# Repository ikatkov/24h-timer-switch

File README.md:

# 24h timer switch

# Fabrication

See kicad files.

## BOM
| Id | Designator | Package | Designation | Value | 
| ------------- | ------------- | ------------- | ------------- |------------- |

## PCB

<a href="https://oshpark.com/shared_projects/55EIuuMn"></img></a>

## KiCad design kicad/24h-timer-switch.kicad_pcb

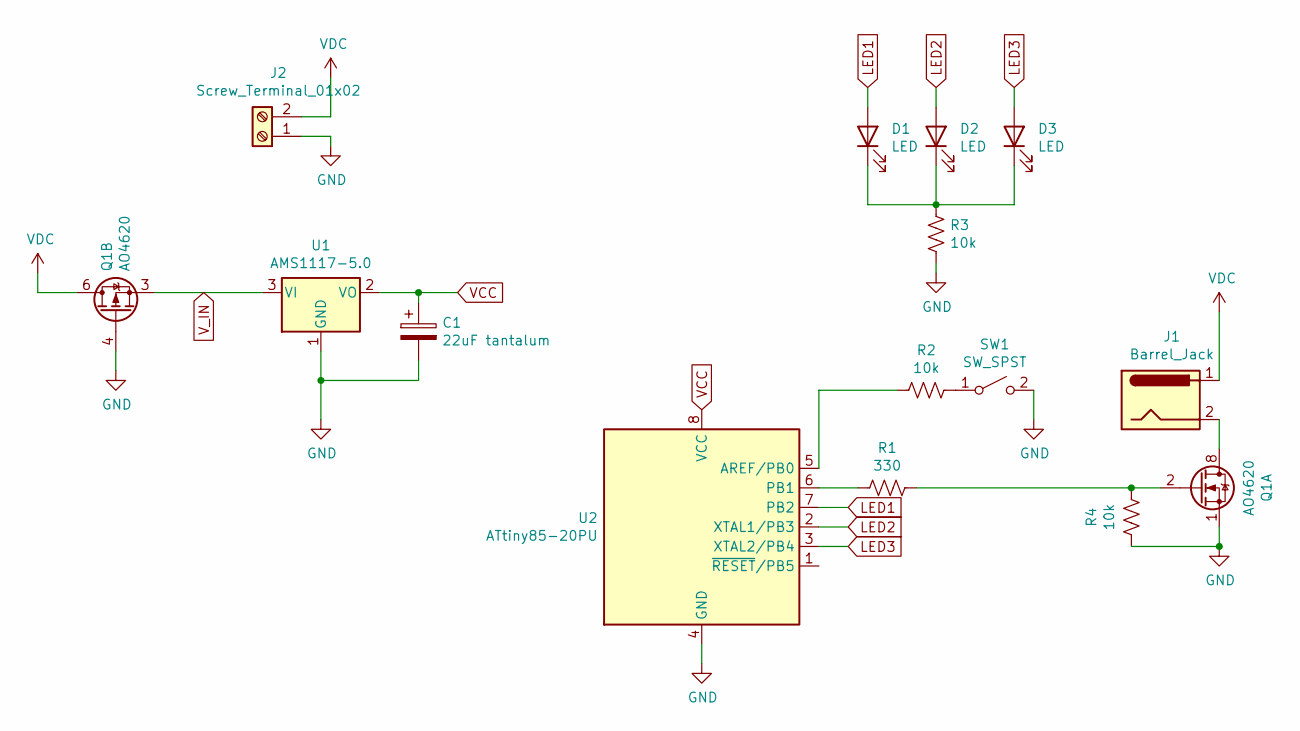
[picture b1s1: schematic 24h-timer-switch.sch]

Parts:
C1: 22uF tantalum; CP_Radial_D5.0mm_P2.50mm
D1, D2, D3: LED; LED_D5.0mm
J1: Barrel_Jack; BarrelJack_Horizontal
J2: Screw_Terminal_01x02; TerminalBlock_MetzConnect_Type011_RT05502HBWC_1x02_P5.00mm_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
Q1: AO4620; SOIC-8_3.9x4.9mm_P1.27mm
R1: 330; R_Axial_DIN0207_L6.3mm_D2.5mm_P2.54mm_Vertical
R2, R3, R4: 10k; R_Axial_DIN0207_L6.3mm_D2.5mm_P2.54mm_Vertical
SW1: SW_SPST; SW_PUSH_6mm_H9.5mm
U1: AMS1117-5.0; SOT-223-3_TabPin2
U2: ATtiny85-20PU; DIP-8_W7.62mm

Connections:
GND: C1.2, J2.1, Q1.1 (S), Q1.4 (G), R3.2, R4.2, SW1.2 (B), U1.1 (GND), U2.4 (GND)
LED1: D1.2 (A), U2.7 (PB2)
LED2: D2.2 (A), U2.2 (XTAL1/PB3)
LED3: D3.2 (A), U2.3 (XTAL2/PB4)
unnamed: D1.1 (K), D2.1 (K), D3.1 (K), R3.1
unnamed: J1.2, Q1.7 (D), Q1.8 (D)
unnamed: Q1.2 (G), R1.1, R4.1
unnamed: R1.2, U2.6 (PB1)
unnamed: R2.1, SW1.1 (A)
unnamed: R2.2, U2.5 (AREF/PB0)
VCC: C1.1, U1.2 (VO), U2.8 (VCC)
VDC: J1.1, J2.2, Q1.5 (D), Q1.6 (D)
V_IN: Q1.3 (1), U1.3 (VI)

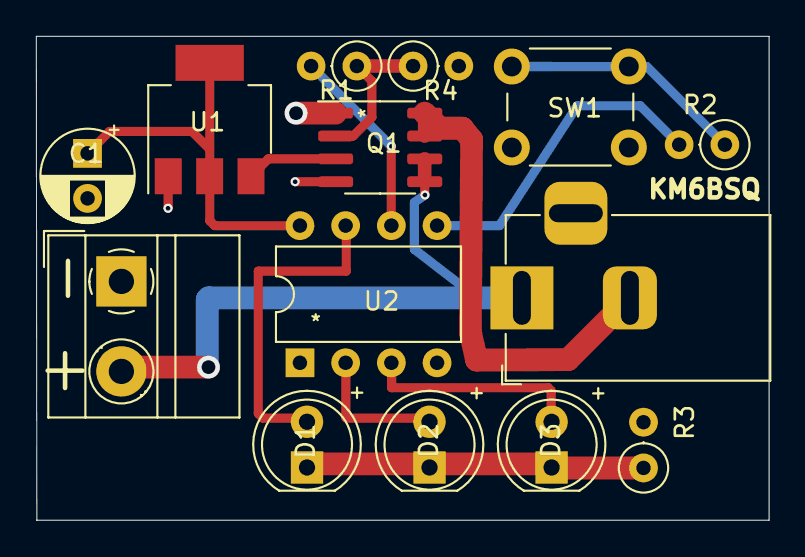
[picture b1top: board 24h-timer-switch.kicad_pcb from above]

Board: 2 copper layers, 40.7 x 26.9 mm, 14 parts (0 on the bottom side), 13 nets.

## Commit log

2021-11-28 gerbers
2021-11-28 add jumper selector
2021-11-28 better routing
2021-12-19 full-board
2021-12-20 timer is off
2021-12-20 working code
2021-12-20 new hardware
2021-12-20 new render
